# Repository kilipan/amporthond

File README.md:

# Amporthond
An ortholinear drop-in PCB for the Ampersand keyboard.

## WIP repo

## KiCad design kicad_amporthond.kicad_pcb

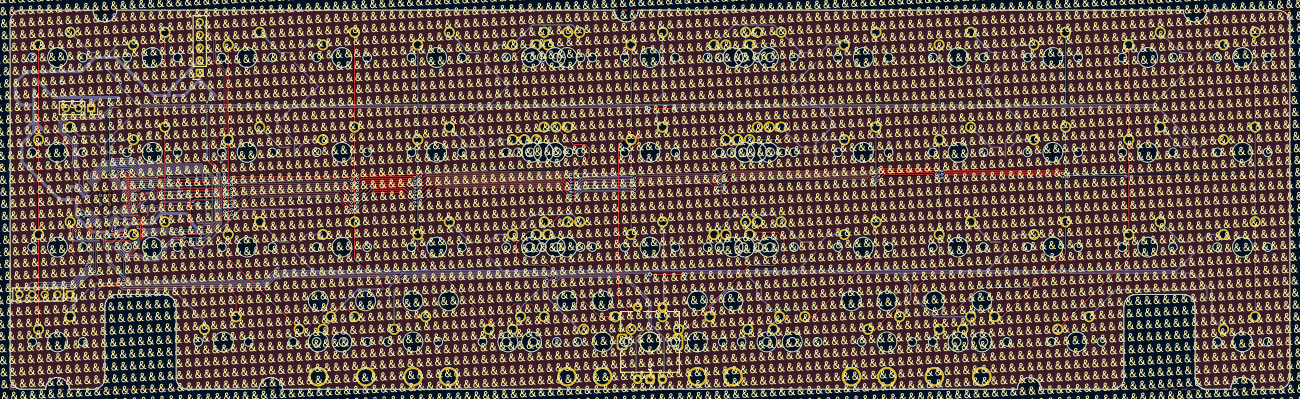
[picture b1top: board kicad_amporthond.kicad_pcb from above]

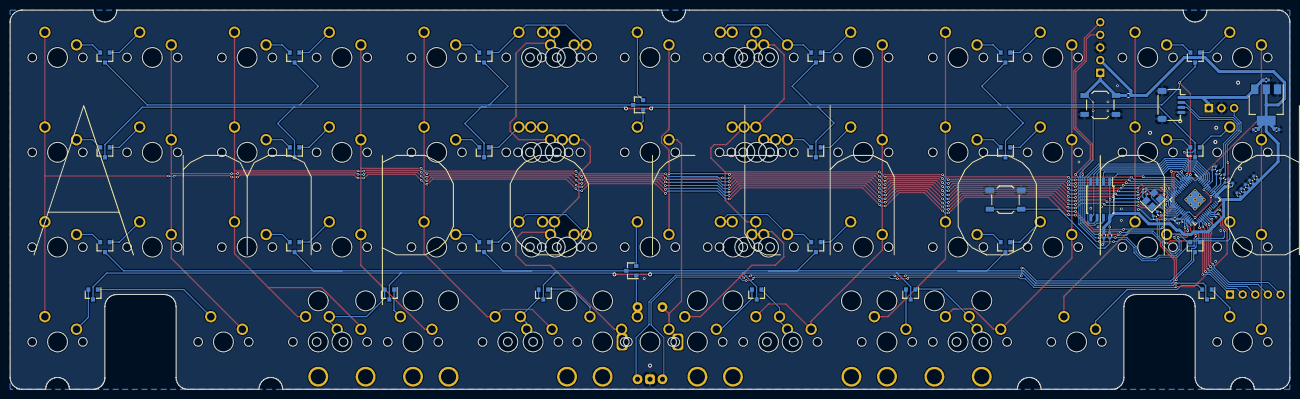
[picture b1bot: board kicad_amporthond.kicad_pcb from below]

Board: 2 copper layers, 257.2 x 76.2 mm, 130 parts (53 on the bottom side), 99 nets.

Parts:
C1, C4, C6: 10u; C_0402_1005Metric
C2, C3: 22pf; C_0402_1005Metric
C5, C7, C9, C11, C12, C13, C14, C15: 100n; C_0402_1005Metric
C8, C10: 1u; C_0402_1005Metric
D1, D2, D3, D4, D5, D6, D7, D8, D9, D10, D11, D12, D13, D14, D15, D16, D17, D18, D19, D20, D21, D22, D23, D24, D25, D26: BAV70; SOT-23
J1: Conn_01x02_Female; PinSocket_1x05_P2.54mm_Vertical
J3: Conn_01x03_Male; PinSocket_1x03_P2.54mm_Vertical
J4: BREAKOUT; PinSocket_1x05_P2.54mm_Vertical
J6: Conn_01x04; JST_SH_SM04B-SRSS-TB_1x04-1MP_P1.00mm_Horizontal
MX1, MX2, MX3, MX4, MX5, MX6, MX7, MX8, MX9, MX10, MX11, MX12, MX13, MX14, MX15, MX16, MX17, MX18, MX19, MX20, MX21, MX22, MX23, MX24, MX25, MX26, MX27, MX28, MX29, MX30, MX31, MX32, MX33, MX34, MX35, MX36, MX37, MX38, MX39, MX40, MX41, MX42, MX43, MX44, MX45, MX46, MX47, MX48, MX49, MX50, MX51, MX58, MX63, MX64, MX65, MX66, MX67, MX68: MX_SW_HS; SW_MX_1u
MX52, MX53, MX56, MX57: MX_SW_HS; SW_MX_1.75u
MX54, MX55: MX_SW_HS; SW_MX_1.25u
MX59, MX60, MX61, MX62: MX_SW_HS; SW_MX_1.5u
R1, R3: 1k; R_0402_1005Metric
R2: 10K; R_0402_1005Metric
R4, R5: 27; R_0402_1005Metric
S1: MX_stab; STAB_MX_P_10u
S2, S3: MX_stab; STAB_MX_P_2u
S4, S5: MX_stab; STAB_MX_P_3u
SW1: RotaryEncoder_Switch; ROT_Alps_EC11E-Switch
SW2: SW_PUSH; SW_SPST_TL3342
SW3: RESET; SW_SPST_TL3342
U1: NCP1117-3.3_SOT223; SOT-223-3_TabPin2
U2: RP2040; RP2040-QFN-56
U3: W25Q128JVS; SOIC-8_5.23x5.23mm_P1.27mm
Y1: 12MHZ Crystal; Crystal_SMD_3225-4Pin_3.2x2.5mm

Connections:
+1V1: C5.1, C7.1, C8.1, U2.23 (DVDD), U2.45 (VREG_VOUT), U2.50 (DVDD)
+3V3: C4.1, C6.1, C9.1, C10.1, C11.1, C12.1, C13.1, C14.1, C15.1, J4.2, R2.2, U1.2 (VO), U2.1 (IOVDD), U2.10 (IOVDD), U2.22 (IOVDD), U2.33 (IOVDD), U2.42 (IOVDD), U2.43 (ADC_AVDD), U2.44 (VREG_IN), U2.48 (USB_VDD), U2.49 (IOVDD), U3.8 (VCC)
+5V: C1.1, J3.1, J6.1, U1.3 (VI)
/QSPI_SCLK: U2.52 (QSPI_SCLK), U3.6 (CLK)
/QSPI_SD0: U2.53 (QSPI_SD0), U3.5 (DI(IO0))
/QSPI_SD1: U2.55 (QSPI_SD1), U3.2 (DO(IO1))
/QSPI_SD2: U2.54 (QSPI_SD2), U3.3 (IO2)
/QSPI_SD3: U2.51 (QSPI_SD3), U3.7 (IO3)
/QSPI_SS: R3.1, U2.56 (QSPI_SS), U3.1 (~CS)
/RUN: J4.1, R2.1, SW2.2, U2.26 (RUN)
/SWCLK: J4.5, U2.24 (SWCLK)
/SWD: J4.4, U2.25 (SWD)
/USB_D+: J6.3, R4.1
/USB_D-: J6.2, R5.1
/XIN: C2.1, U2.20 (XIN), Y1.3
/XOUT: R1.1, U2.21 (XOUT)
/~USB_BOOT: R3.2, SW3.2
ENC_L: SW1.A, U2.37 (GPIO25)
ENC_R: SW1.B, U2.36 (GPIO24)
GND: C1.2, C2.2, C3.2, C4.2, C5.2, C6.2, C7.2, C8.2, C9.2, C10.2, C11.2, C12.2, C13.2, C14.2, C15.2, J3.2, J4.3, J6.4, J6.MP, SW1.C, SW2.1, SW3.1, U1.1 (GND), U2.19 (TESTEN), U2.57 (GND), U3.4 (GND), Y1.2, Y1.4
LED_GLOW: J3.3, U2.35 (GPIO23)
unnamed: C3.1, R1.2, Y1.1
unnamed: D1.1 (A), MX1.2
unnamed: D1.2 (A), MX2.1
unnamed: D2.1 (A), MX3.2
unnamed: D2.2 (A), MX4.1
unnamed: D3.1 (A), MX5.2
unnamed: D3.2 (A), MX6.1, MX52.2, MX63.2
unnamed: D4.1 (A), MX7.2, MX53.1, MX64.1
unnamed: D4.2 (A), MX8.1
unnamed: D5.1 (A), MX9.2
unnamed: D5.2 (A), MX10.1
unnamed: D6.1 (A), MX11.2
unnamed: D6.2 (A), MX12.1
unnamed: D7.1 (A), MX14.2
unnamed: D7.2 (A), MX15.1
unnamed: D8.1 (A), MX16.2
unnamed: D8.2 (A), MX17.1
unnamed: D9.1 (A), MX18.2
unnamed: D9.2 (A), MX19.1, MX54.1, MX65.1
unnamed: D10.1 (A), MX20.2, MX55.2, MX67.2
unnamed: D10.2 (A), MX21.1
unnamed: D11.1 (A), MX22.2
unnamed: D11.2 (A), MX23.1
unnamed: D12.1 (A), MX24.2
unnamed: D12.2 (A), MX25.1
unnamed: D13.1 (A), MX27.2
unnamed: D13.2 (A), MX28.1
unnamed: D14.1 (A), MX29.2
unnamed: D14.2 (A), MX30.1
unnamed: D15.1 (A), MX31.2
unnamed: D15.2 (A), MX32.1, MX56.2, MX66.2
unnamed: D16.1 (A), MX33.2, MX57.1, MX68.1
unnamed: D16.2 (A), MX34.1
unnamed: D17.1 (A), MX35.2
unnamed: D17.2 (A), MX36.1
unnamed: D18.1 (A), MX37.2
unnamed: D18.2 (A), MX38.1
unnamed: D19.1 (A), MX40.2
unnamed: D19.2 (A), MX51.1
unnamed: D20.1 (A), MX41.2, MX59.1
unnamed: D20.2 (A), MX42.1
unnamed: D21.1 (A), MX43.2, MX61.1
unnamed: D21.2 (A), MX44.1
unnamed: D22.1 (A), MX45.2
unnamed: D22.2 (A), MX46.1, MX62.2
unnamed: D23.1 (A), MX47.2
unnamed: D23.2 (A), MX48.1, MX60.2
unnamed: D24.1 (A), MX49.2
unnamed: D24.2 (A), MX50.1
unnamed: D25.1 (A), MX26.2
unnamed: D25.2 (A), MX13.2
unnamed: D26.1 (A), MX58.2, SW1.S1
unnamed: D26.2 (A), MX39.2
unnamed: R5.2, U2.46 (USB_DM)
unnamed: R4.2, U2.47 (USB_DP)
c0: MX1.1, MX14.1, MX27.1, MX40.1, U2.6 (GPIO4)
c1: MX2.2, MX15.2, MX28.2, MX51.2, U2.7 (GPIO5)
c2: MX3.1, MX16.1, MX29.1, MX41.1, MX59.2, U2.8 (GPIO6)
c3: MX4.2, MX17.2, MX30.2, MX42.2, U2.9 (GPIO7)
c4: MX5.1, MX18.1, MX31.1, MX43.1, MX61.2, U2.11 (GPIO8)
c5: MX6.2, MX19.2, MX32.2, MX44.2, MX52.1, MX54.2, MX56.1, MX63.1, MX65.2, MX66.1, U2.12 (GPIO9)
c6a: MX13.1, MX39.1, U2.13 (GPIO10)
c6b: MX26.1, MX58.1, SW1.S2, U2.14 (GPIO11)
c7: MX7.1, MX20.1, MX33.1, MX45.1, MX53.2, MX55.1, MX57.2, MX64.2, MX67.1, MX68.2, U2.15 (GPIO12)
c8: MX8.2, MX21.2, MX34.2, MX46.2, MX62.1, U2.16 (GPIO13)
c9: MX9.1, MX22.1, MX35.1, MX47.1, U2.17 (GPIO14)
c10: MX10.2, MX23.2, MX36.2, MX48.2, MX60.1, U2.18 (GPIO15)
c11: MX11.1, MX24.1, MX37.1, MX49.1, U2.27 (GPIO16)
c12: MX12.2, MX25.2, MX38.2, MX50.2, U2.28 (GPIO17)
extra_pin1: J1.1, U2.29 (GPIO18)
extra_pin2: J1.2, U2.30 (GPIO19)
extra_pin3: J1.3, U2.31 (GPIO20)
extra_pin4: J1.4, U2.32 (GPIO21)
extra_pin5: J1.5, U2.34 (GPIO22)
r0: D1.3 (K), D2.3 (K), D3.3 (K), D4.3 (K), D5.3 (K), D6.3 (K), D25.3 (K), U2.2 (GPIO0)
r1: D7.3 (K), D8.3 (K), D9.3 (K), D10.3 (K), D11.3 (K), D12.3 (K), U2.3 (GPIO1)
r2: D13.3 (K), D14.3 (K), D15.3 (K), D16.3 (K), D17.3 (K), D18.3 (K), D26.3 (K), U2.4 (GPIO2)
r3: D19.3 (K), D20.3 (K), D21.3 (K), D22.3 (K), D23.3 (K), D24.3 (K), U2.5 (GPIO3)
